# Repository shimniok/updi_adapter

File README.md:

# 6-Pin Serial to UPDI Adapter

A simple adapter board that converts any 6-pin USB to serial adapter to an Atmel AVR UPDI programmer with the use of [pymcuprog](https://pypi.org/project/pymcuprog/).

To program your tinyAVR 0/1/2 series device with Arduino IDE, you'll want to use Spence Konde's excellent [megaTinyCore](https://github.com/SpenceKonde/megaTinyCore).

Examples of 6-pin USB to serial adapters are typically based on [FTDI FT232](https://ftdichip.com/products/ft232rl/), [Silicon Labs CP210x](https://www.silabs.com/interface/usb-bridges/classic/device.cp2102), or [WCH CH340](http://www.wch-ic.com/products/CH340.html?from=list) integrated circuits.

My recommendations:

* [Sparkfun Basic Breakout, USB C / CH340](https://www.sparkfun.com/products/15096)
* [Sparkfun Basic Breakout, 5V FTDI](https://www.sparkfun.com/products/9716)
* [Adafruit FTDI Friend](https://www.adafruit.com/product/284)

Although you can find cheap versions on eBay, AliExpress, Amazon, etc., you might run into issues. For potential pitfalls and other guidance, refer to [Spence Konde's UPDI guide](https://github.com/SpenceKonde/AVR-Guidance/blob/master/UPDI/jtag2updi.md)

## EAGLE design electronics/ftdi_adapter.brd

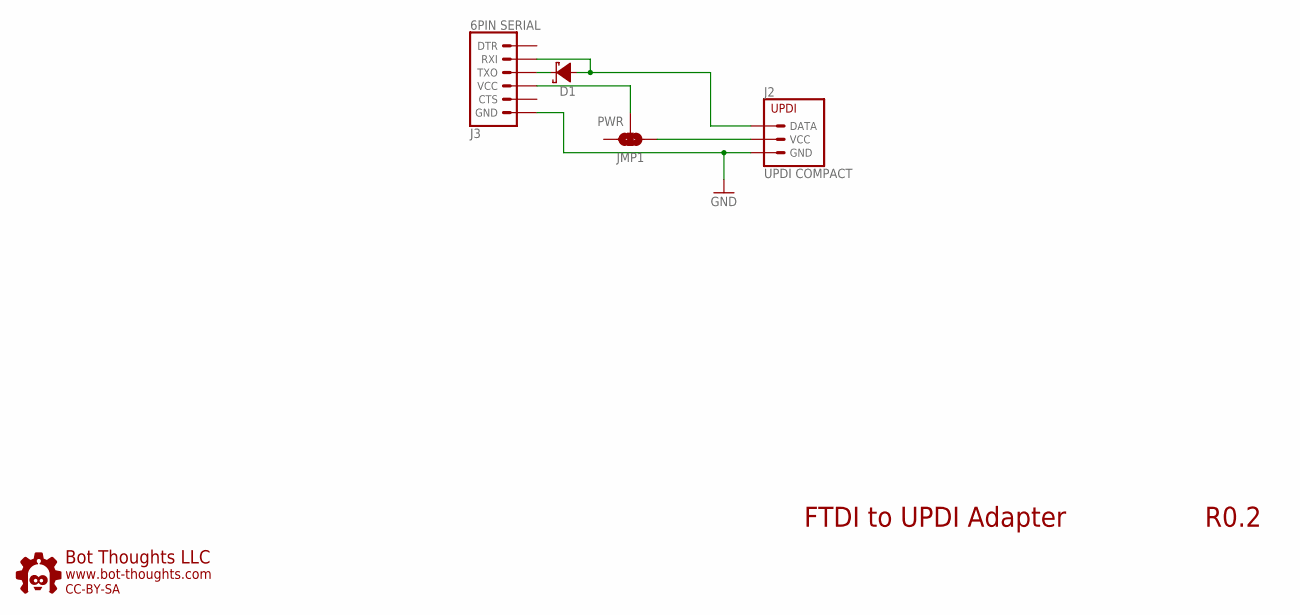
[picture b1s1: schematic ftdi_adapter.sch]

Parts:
D1: DIODE-SCHOTTKYSOD-323ORIG; SOD-323ORIG
J2: UPDI COMPACT; UPDI_1X3
J3: 6PIN SERIAL; 6PIN_TARGET
JMP1: PWR; JUMPER-2W-PIN-0.1IN
U$1: BTLOGO-LOGO-SM; BTLOGOS

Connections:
DATA: D1.A, J2.3 (DATA), J3.2 (RXI)
GND: J2.2 (GND), J3.6 (GND)
unnamed: D1.C, J3.3 (TXO)
unnamed: J3.4 (VCC), JMP1.2
VCC: J2.1 (VCC), JMP1.1

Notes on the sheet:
FTDI to UPDI Adapter
R0.2

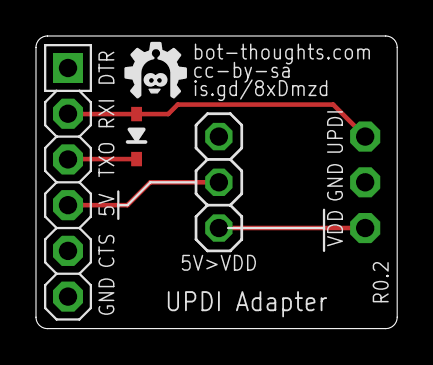
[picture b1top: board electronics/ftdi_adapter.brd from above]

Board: 2 copper layers, 20.1 x 16.3 mm, 5 parts (1 on the bottom side), 5 nets.

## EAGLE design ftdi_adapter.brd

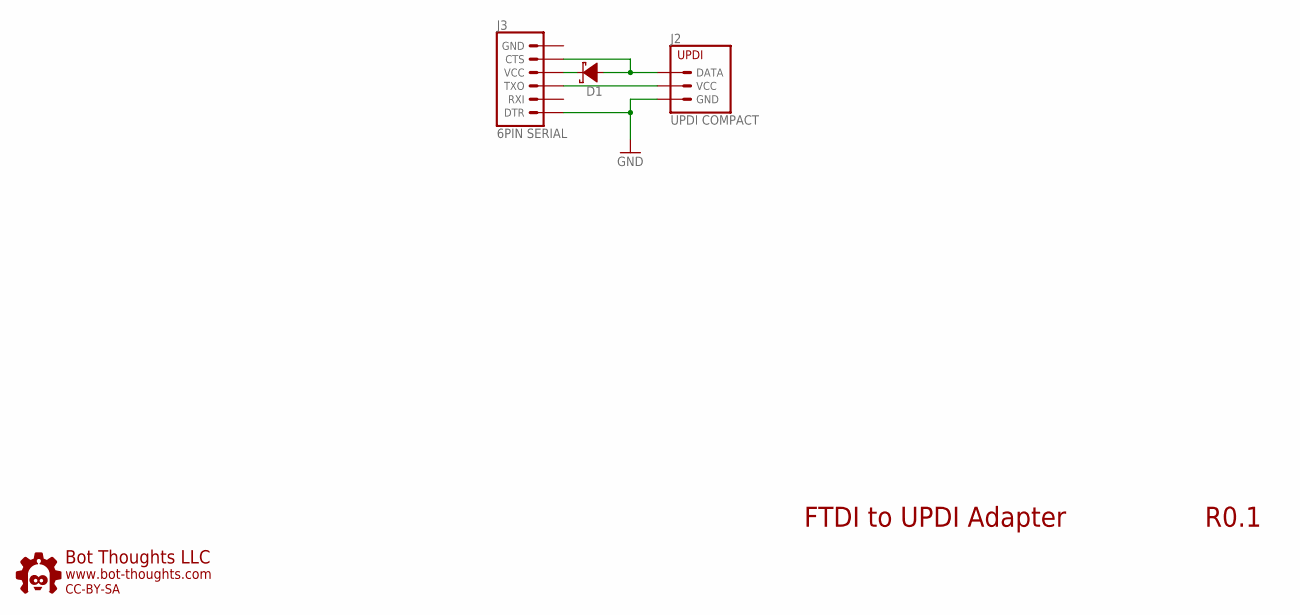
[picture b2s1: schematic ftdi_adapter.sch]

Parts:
D1: DIODE-SCHOTTKYSOD-323ORIG; SOD-323ORIG
J2: UPDI COMPACT; UPDI_1X3
J3: 6PIN SERIAL; 6PIN_TARGET
U$1: BTLOGO-LOGO-SM; BTLOGOS

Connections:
GND: J2.2 (GND), J3.1 (DTR)
unnamed: D1.C, J3.4 (VCC)
unnamed: D1.A, J2.3 (DATA), J3.5 (CTS)
VCC: J2.1 (VCC), J3.3 (TXO)

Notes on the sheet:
FTDI to UPDI Adapter
R0.1

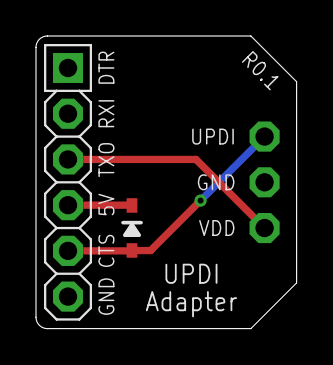
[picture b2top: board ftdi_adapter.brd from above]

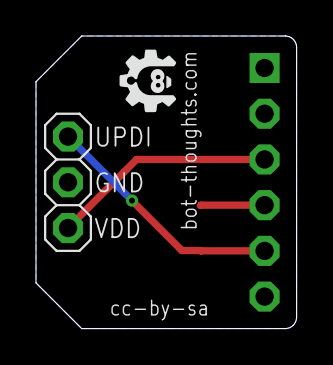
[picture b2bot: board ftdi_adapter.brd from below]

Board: 2 copper layers, 14.5 x 16.3 mm, 4 parts (2 on the bottom side), 4 nets.

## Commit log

2022-05-03 add documentation readme
2022-05-03 initial version
2022-05-03 updated gitignore, moved files to electronics subdir
2022-05-03 added gerbers, zip
2022-05-03 updated documentation
2022-05-03 removed documentation, will use main readme
2022-05-03 added help url
2022-05-03 updated zip
2022-05-03 Updated version #

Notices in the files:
electronics/ftdi_adapter.brd:
cc-by-sa
